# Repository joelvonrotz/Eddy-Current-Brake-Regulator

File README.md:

# Eddy Current Brake Regulator
This Repository is for the storage of all files and references used in the documentation.
Additionally the mechanical plans, KiCAD files, used for the PCB, and the Latex Project is included here.

# Geregelte Wirbelstrombremse
Dieses *Repository* beinhaltet alle verwendeten Informationen bezüglich der Maturaarbeit *Geregelte Wirbelstrombremse*. Alle mechanischen Pläne, Leiterplattendaten und das Latex-Projekt selber wird hier abgespeichert.

:warning: This is my very first Latex-project, so expect a lot of workarounds :warning:

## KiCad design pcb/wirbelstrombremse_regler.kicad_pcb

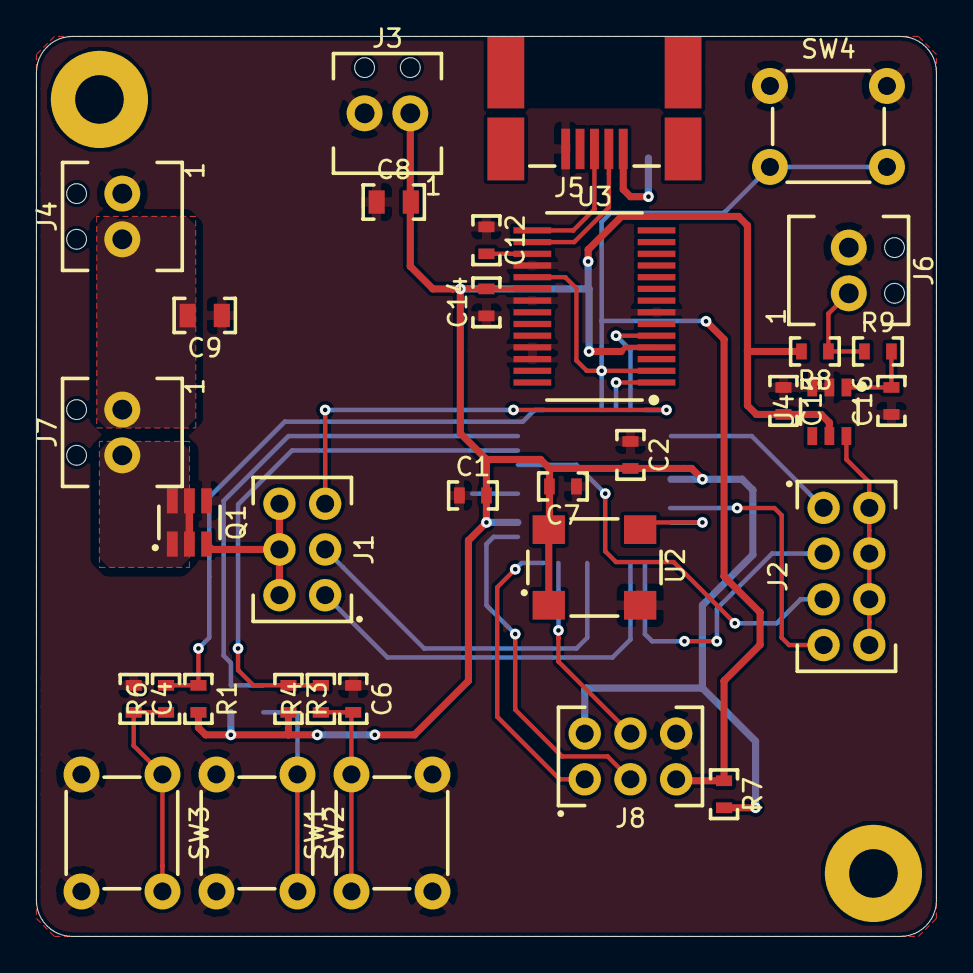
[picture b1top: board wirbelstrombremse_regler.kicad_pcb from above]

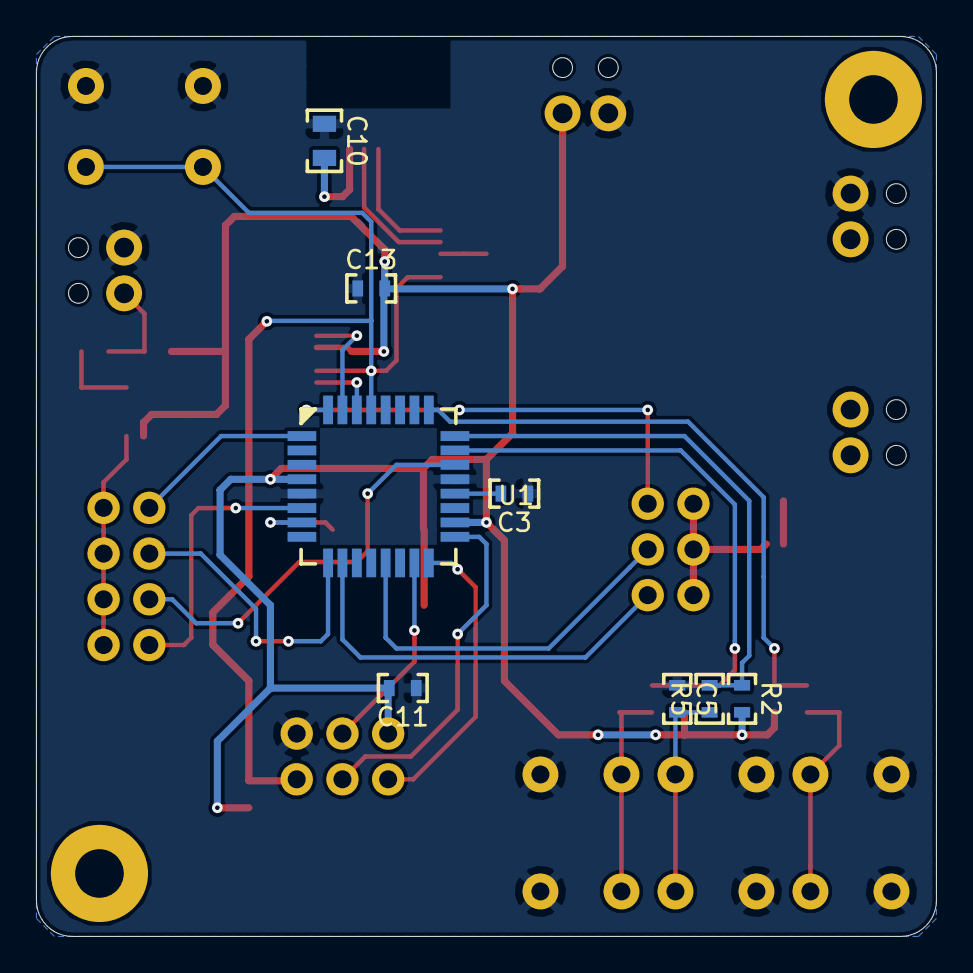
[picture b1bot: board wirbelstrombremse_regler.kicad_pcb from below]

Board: 2 copper layers, 50.0 x 50.0 mm, 44 parts (8 on the bottom side), 33 nets.

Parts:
C1, C2, C3, C4, C5, C6, C7, C11, C12, C13, C14, C15, C16: CAP_100nF_0603; CAP_0603
C8, C9, C10: CAP_10uF_0805; CAP_0805
H1, H2: HOLE_2.7mm
J1, J8: SL_100mil_2x3p; SL_100MIL_2x3p
J2: SL_100mil_2x4p; SL_100MIL_2x4p
J3, J4, J6, J7: CON_PHOENIX_1725656; CON_MPT_1725656
J5: CON_MOLEX_548190572; MOLEX_54819_0572
Q1: MOSFET_CPH6442; ONSEMI_318BD
R1, R2, R3, R4, R5, R6, R7, R8, R9: RES_10k_0603; RES_0603
SW1, SW2, SW3, SW4: BUT_B3F-1022; BUT_B3F-10XX
U1: ATMEGA328PB-AU; TQFP32_7x7_800
U2: OSZ_LFSPXO019275; IQD_CFPS-72
U3: FT232RL-REEL; SSOP-28
U4: SN74LVC2G14; SOT-23-6

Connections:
+5V: C1.1, C2.1, C7.1, C8.1, C11.1, C13.1, C14.1, C15.1, J3.1, J8.2, R1.1, R2.1, R3.1, R7.1, R8.1, U1.4, U1.18, U2.1, U2.4, U3.4, U3.20, U4.5
+UPOW: C9.1, J4.2, J7.1
/Connector/MAGNET: J7.2, Q1.1, Q1.2, Q1.5, Q1.6
/Connector/MCU_RESET: J8.5, R7.2, SW4.3, SW4.4, U1.29, U3.2, U3.19
/Connector/MCU_SensorSpeed: J2.2, J2.4, J2.6, J2.8, U4.6
/Connector/PROG_MISO: J8.1, U1.16
/Connector/PROG_MOSI: J8.4, U1.15
/Connector/PROG_SCK: J8.3, U1.17
/Connector/SensorSpeed: C16.1, R9.1, U4.1
/Connector/USB+: J5.3, U3.15
/Connector/USB-: J5.2, U3.16
/MicroControl/EXINT: J2.1, U1.1
/MicroControl/FET: J1.2, J1.4, J1.6, Q1.3
/MicroControl/MCU_RX: U1.30, U3.1
/MicroControl/MCU_TX: U1.31, U3.5
/MicroControl/OSC_IN: U1.7, U2.3
/MicroControl/OUT0: J1.1, U1.10
/MicroControl/OUT1: J1.3, U1.13
/MicroControl/OUT3_4: J1.5, U1.32
/MicroControl/PCINT_DEC: R2.2, R5.1, U1.24
/MicroControl/PCINT_INC: R1.2, R6.1, U1.25
/MicroControl/PCINT_SET: R3.2, R4.1, U1.23
/MicroControl/T1: J2.3, U1.9
/MicroControl/T3: J2.5, U1.22
/MicroControl/T4: J2.7, U1.6
GND: C1.2, C2.2, C3.2, C4.2, C5.2, C6.2, C7.2, C8.2, C9.2, C10.2, C11.2, C12.2, C13.2, C14.2, C15.2, C16.2, J3.2, J4.1, J5.5, J6.2, J8.6, Q1.4, SW1.3, SW1.4, SW2.3, SW2.4, SW3.3, SW3.4, SW4.1, SW4.2, U1.5, U1.21, U2.2, U3.7, U3.18, U3.21, U3.25, U3.26, U4.2, U4.3
unnamed: C3.1, U1.20
unnamed: C4.1, R6.2, SW3.1, SW3.2
unnamed: C5.1, R5.2, SW2.1, SW2.2
unnamed: C6.1, R4.2, SW1.1, SW1.2
unnamed: C10.1, J5.1
unnamed: C12.1, U3.17
unnamed: J6.1, R8.2, R9.2

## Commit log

2019-02-14 added german
2019-02-14 added attachment files
2019-02-14 added more files
2019-02-14 added code
    help me jesus
2019-02-15 added pcb and plans
